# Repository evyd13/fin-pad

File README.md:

# Fin Pad

Replacement PCB for Lin Dolphin Pad.

## License

Read the license before use!

## Gerbers

Gerber zip files can be found under `gerber/`.

## BOM

| LCSC part # | Description   | Value | Package  | Amount |
| ----------- | ------------- | ----- | -------- | ------:|
| C14663      | Capacitor     | 0.1uF | 0603     | 3      |
| C19666      | Capacitor     | 4.7uF | 0603     | 1      |
| C15849      | Capacitor     | 1uF   | 0603     | 1      |
| C2128       | Switch diode  | 4148  | 0805     | 24     |
| C261942     | Fuse          |       | 0805     | 1      |
| C165948     | Type-C con.   |       | SMD+TH   | 1      |
| C25804      | Resistor      | 10K   | 0603     | 2      |
| C23345      | Resistor      | 22    | 0603     | 2      |
| C23186      | Resistor      | 5.1k  | 0603     | 2      |
| C7519       | ESD prot.     |       | SOT23-6  | 1      |
| C1337609    | MCU           | 32U2  | QFP-32   | 1      |
| C341521     | Resonator     | 16MHz | SMD      | 1      |
| C92584      | Switch        |       | SMD      | 1      |

Use at your own risk.

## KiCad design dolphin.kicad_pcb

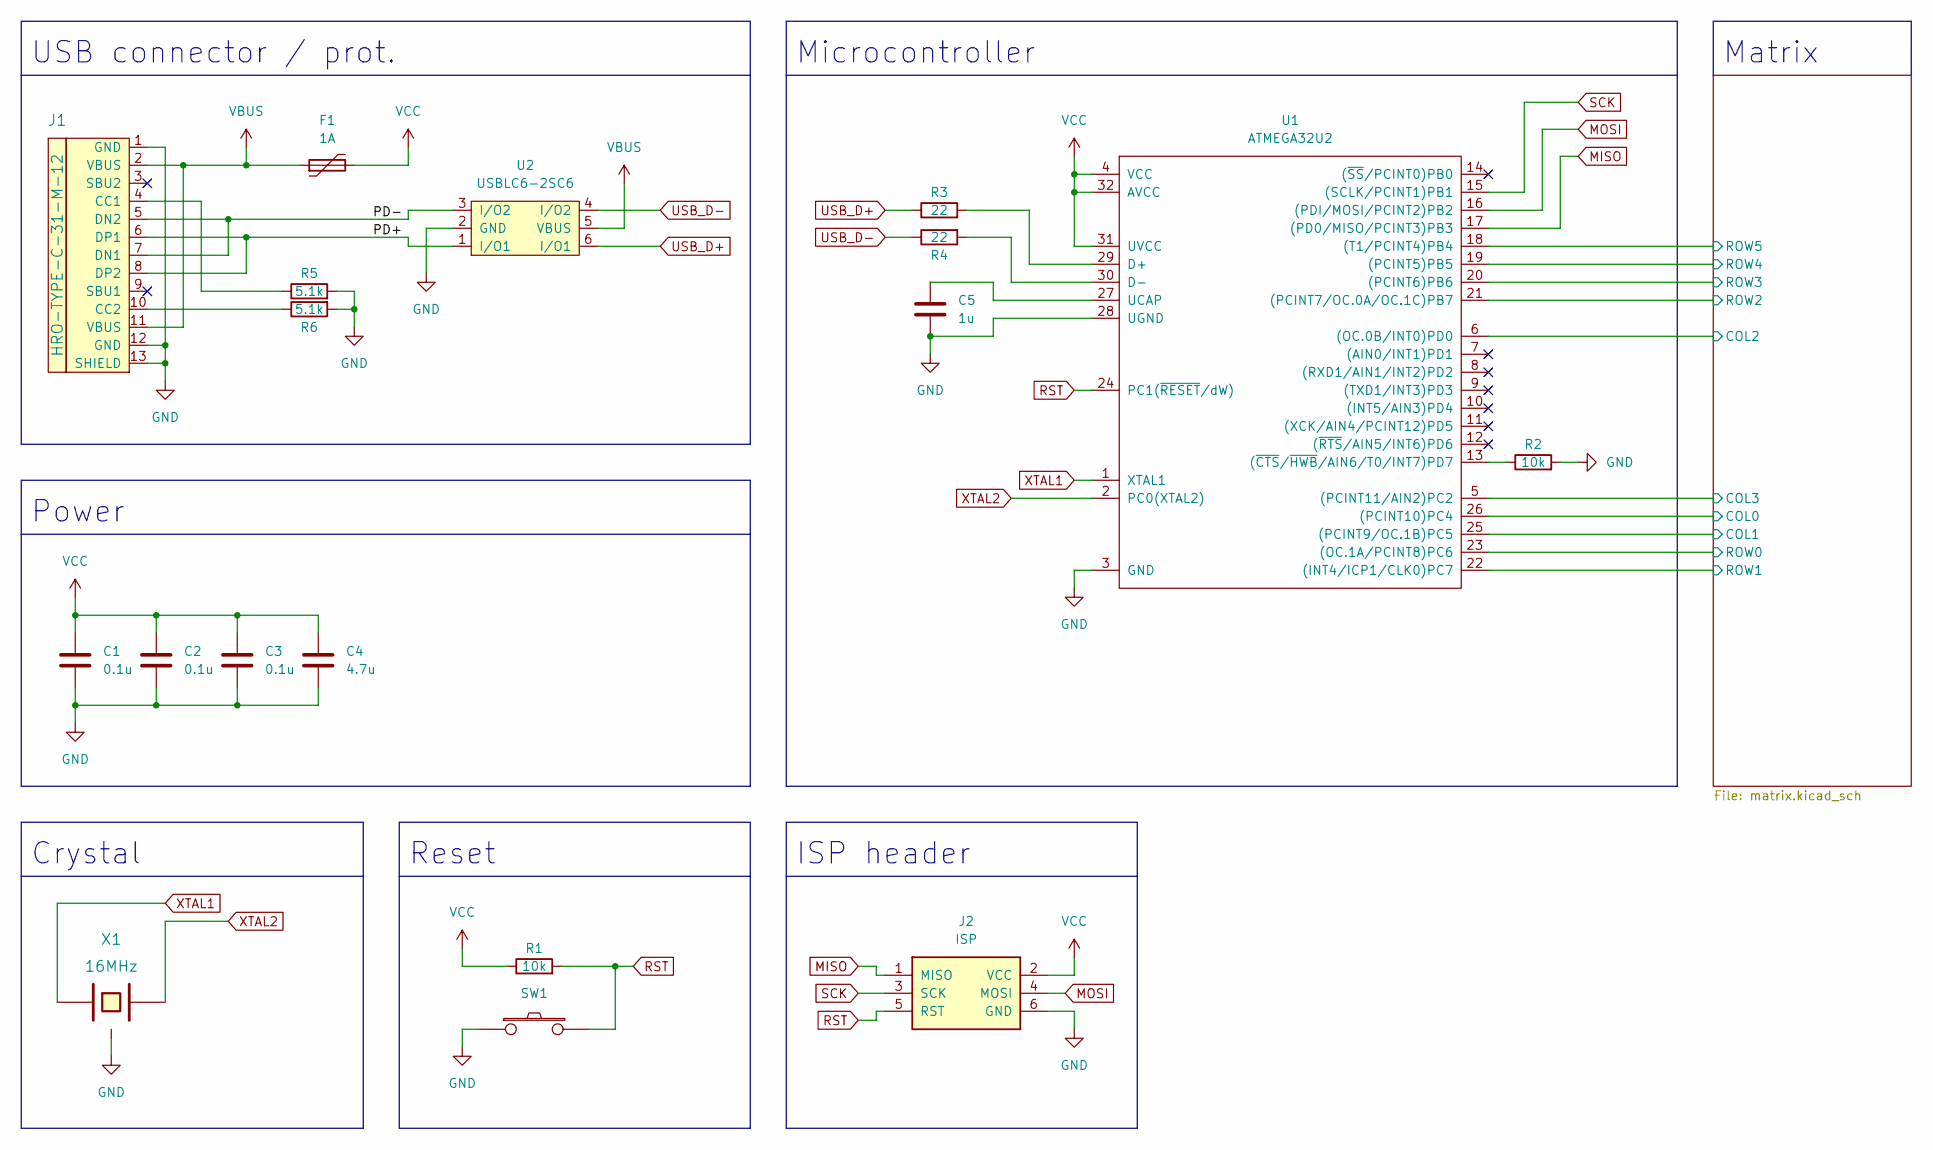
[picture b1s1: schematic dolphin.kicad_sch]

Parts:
C1, C2, C3: 0.1u; C_0603; Part number CC0603KRX7R9BB104; LCSC Part C14663
C4: 4.7u; C_0603; Part number CL10A475KO8NNNC; LCSC Part C19666
C5: 1u; C_0603; Part number CL10A105KB8NNNC; LCSC Part C15849
F1: 1A; R_0805; Part number TLC-PSMD050; LCSC Part C261942
J1: HRO-TYPE-C-31-M-12; CONN_HRO-TYPE-C-31-M-12; Part number TYPE-C-31-M-12; LCSC Part C165948
J2: ISP; CONN_isp_standard; JLCPCB BOM 0
R1, R2: 10k; R_0603; Part number 0603WAF1002T5E; LCSC Part C25804
R3, R4: 22; R_0603; Part number 0603WAF220JT5E; LCSC Part C23345
R5, R6: 5.1k; R_0603; Part number 0603WAF5101T5E; LCSC Part C23186
SW1: SW_PUSH; SWITCH_SPST_TL3342; Part number TS-1187A-B-A-B; LCSC Part C318884
U1: ATMEGA32U2; MCU_ATMEGA32U2-AU
U2: USBLC6-2SC6; PACKAGE_SOT-23-6; Part number USBLC6-2SC6; LCSC Part C7519
X1: 16MHz; XTAL_SMD_Murata_CSTxExxV-3Pin_3.0x1.1mm; Part number CSTNE16M0V530000R0; LCSC Part C341521

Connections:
/Matrix/COL0: U1.26 ((PCINT10)PC4); also elsewhere on the board
/Matrix/COL1: U1.25 ((PCINT9/OC.1B)PC5); also elsewhere on the board
/Matrix/COL2: U1.6 ((OC.0B/INT0)PD0); also elsewhere on the board
/Matrix/COL3: U1.5 ((PCINT11/AIN2)PC2); also elsewhere on the board
/Matrix/ROW0: U1.23 ((OC.1A/PCINT8)PC6); also elsewhere on the board
/Matrix/ROW1: U1.22 ((INT4/ICP1/CLK0)PC7); also elsewhere on the board
/Matrix/ROW2: U1.21 ((PCINT7/OC.0A/OC.1C)PB7); also elsewhere on the board
/Matrix/ROW3: U1.20 ((PCINT6)PB6); also elsewhere on the board
/Matrix/ROW4: U1.19 ((PCINT5)PB5); also elsewhere on the board
/Matrix/ROW5: U1.18 ((T1/PCINT4)PB4); also elsewhere on the board
/PD+: J1.6 (DP1), J1.8 (DP2), U2.1 (I/O1)
/PD-: J1.5 (DN2), J1.7 (DN1), U2.3 (I/O2)
GND: C1.2, C2.2, C3.2, C4.2, C5.2, J1.1 (GND), J1.12 (GND), J1.13 (SHIELD), J2.6 (GND), R2.2, R5.2, R6.2, SW1.1, U1.3 (GND), U1.28 (UGND), U2.2 (GND), X1.3
MISO: J2.1 (MISO), U1.17 ((PD0/MISO/PCINT3)PB3)
MOSI: J2.4 (MOSI), U1.16 ((PDI/MOSI/PCINT2)PB2)
unnamed: C5.1, U1.27 (UCAP)
unnamed: J1.4 (CC1), R5.1
unnamed: J1.10 (CC2), R6.1
unnamed: R2.1, U1.13 ((~CTS/~HWB/AIN6/T0/INT7)PD7)
unnamed: R3.2, U1.29 (D+)
unnamed: R4.2, U1.30 (D-)
RST: J2.5 (RST), R1.2, SW1.2, U1.24 (PC1(~RESET/dW))
SCK: J2.3 (SCK), U1.15 ((SCLK/PCINT1)PB1)
USB_D+: R3.1, U2.6 (I/O1)
USB_D-: R4.1, U2.4 (I/O2)
VBUS: F1.1, J1.2 (VBUS), J1.11 (VBUS), U2.5 (VBUS)
VCC: C1.1, C2.1, C3.1, C4.1, F1.2, J2.2 (VCC), R1.1, U1.4 (VCC), U1.31 (UVCC), U1.32 (AVCC)
XTAL1: U1.1 (XTAL1), X1.1
XTAL2: U1.2 (PC0(XTAL2)), X1.2

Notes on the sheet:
Matrix
Microcontroller
Power
Reset
ISP header
Crystal
USB connector / prot.

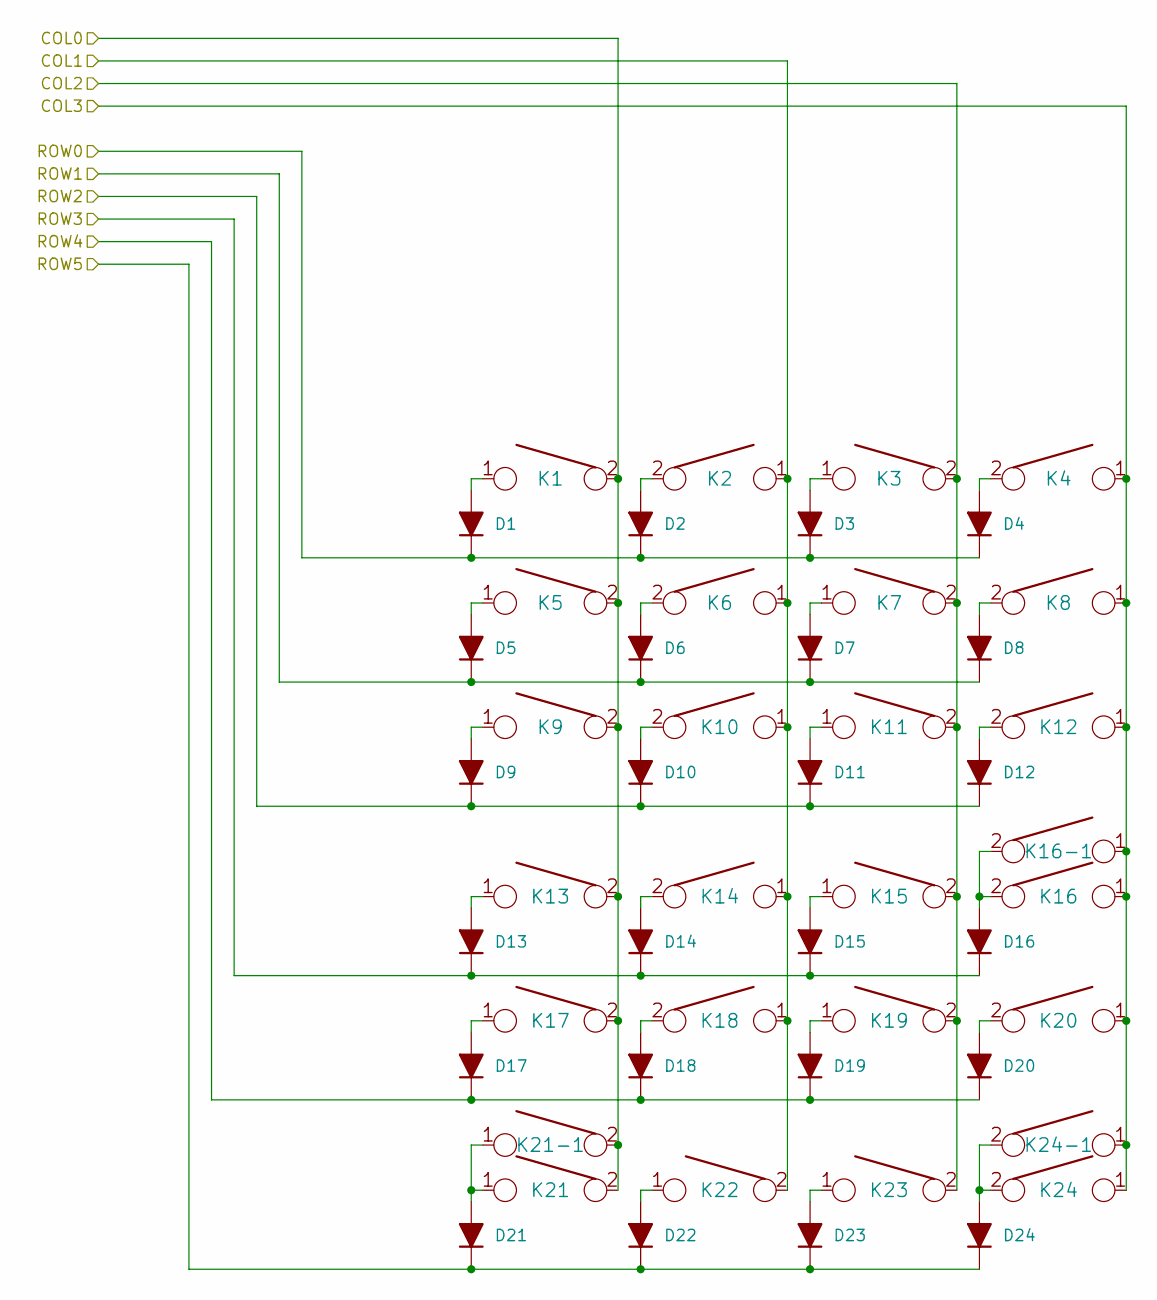
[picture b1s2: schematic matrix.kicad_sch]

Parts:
D1, D2, D3, D4, D5, D6, D7, D8, D9, D10, D11, D12, D13, D14, D15, D16, D17, D18, D19, D20, D21, D22, D23, D24: 4148; D_0805; Part number 1N4148WS; LCSC Part C2128
K1, K2, K3, K4, K5, K6, K7, K8, K9, K10, K11, K12, K13, K14, K15, K16, K17, K18, K19, K20, K21, K22, K23, K24: KEYSW; CHERRY_PLATE_100H; JLCPCB BOM 0
K16-1, K24-1: KEYSW; CHERRY_PCB_200H_V; JLCPCB BOM 0
K21-1: KEYSW; CHERRY_PCB_200H_F; JLCPCB BOM 0

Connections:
/Matrix/COL0: K1.2, K5.2, K9.2, K13.2, K17.2, K21.2, K21-1.2; also elsewhere on the board
/Matrix/COL1: K2.1, K6.1, K10.1, K14.1, K18.1, K22.2; also elsewhere on the board
/Matrix/COL2: K3.2, K7.2, K11.2, K15.2, K19.2, K23.2; also elsewhere on the board
/Matrix/COL3: K4.1, K8.1, K12.1, K16.1, K16-1.1, K20.1, K24.1, K24-1.1; also elsewhere on the board
/Matrix/ROW0: D1.1 (K), D2.1 (K), D3.1 (K), D4.1 (K); also elsewhere on the board
/Matrix/ROW1: D5.1 (K), D6.1 (K), D7.1 (K), D8.1 (K); also elsewhere on the board
/Matrix/ROW2: D9.1 (K), D10.1 (K), D11.1 (K), D12.1 (K); also elsewhere on the board
/Matrix/ROW3: D13.1 (K), D14.1 (K), D15.1 (K), D16.1 (K); also elsewhere on the board
/Matrix/ROW4: D17.1 (K), D18.1 (K), D19.1 (K), D20.1 (K); also elsewhere on the board
/Matrix/ROW5: D21.1 (K), D22.1 (K), D23.1 (K), D24.1 (K); also elsewhere on the board
unnamed: D1.2 (A), K1.1
unnamed: D2.2 (A), K2.2
unnamed: D3.2 (A), K3.1
unnamed: D4.2 (A), K4.2
unnamed: D5.2 (A), K5.1
unnamed: D6.2 (A), K6.2
unnamed: D7.2 (A), K7.1
unnamed: D8.2 (A), K8.2
unnamed: D9.2 (A), K9.1
unnamed: D10.2 (A), K10.2
unnamed: D11.2 (A), K11.1
unnamed: D12.2 (A), K12.2
unnamed: D13.2 (A), K13.1
unnamed: D14.2 (A), K14.2
unnamed: D15.2 (A), K15.1
unnamed: D16.2 (A), K16.2, K16-1.2
unnamed: D17.2 (A), K17.1
unnamed: D18.2 (A), K18.2
unnamed: D19.2 (A), K19.1
unnamed: D20.2 (A), K20.2
unnamed: D21.2 (A), K21.1, K21-1.1
unnamed: D22.2 (A), K22.1
unnamed: D23.2 (A), K23.1
unnamed: D24.2 (A), K24.2, K24-1.2

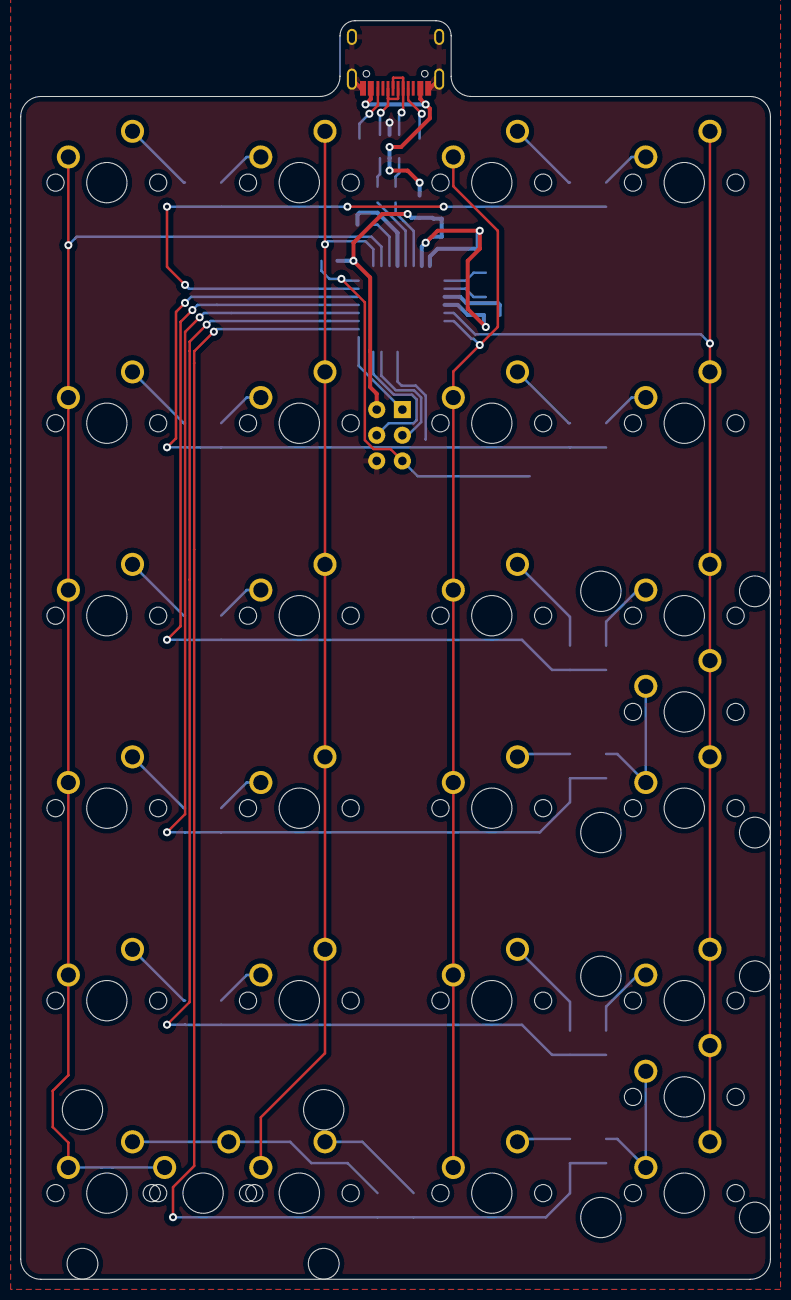
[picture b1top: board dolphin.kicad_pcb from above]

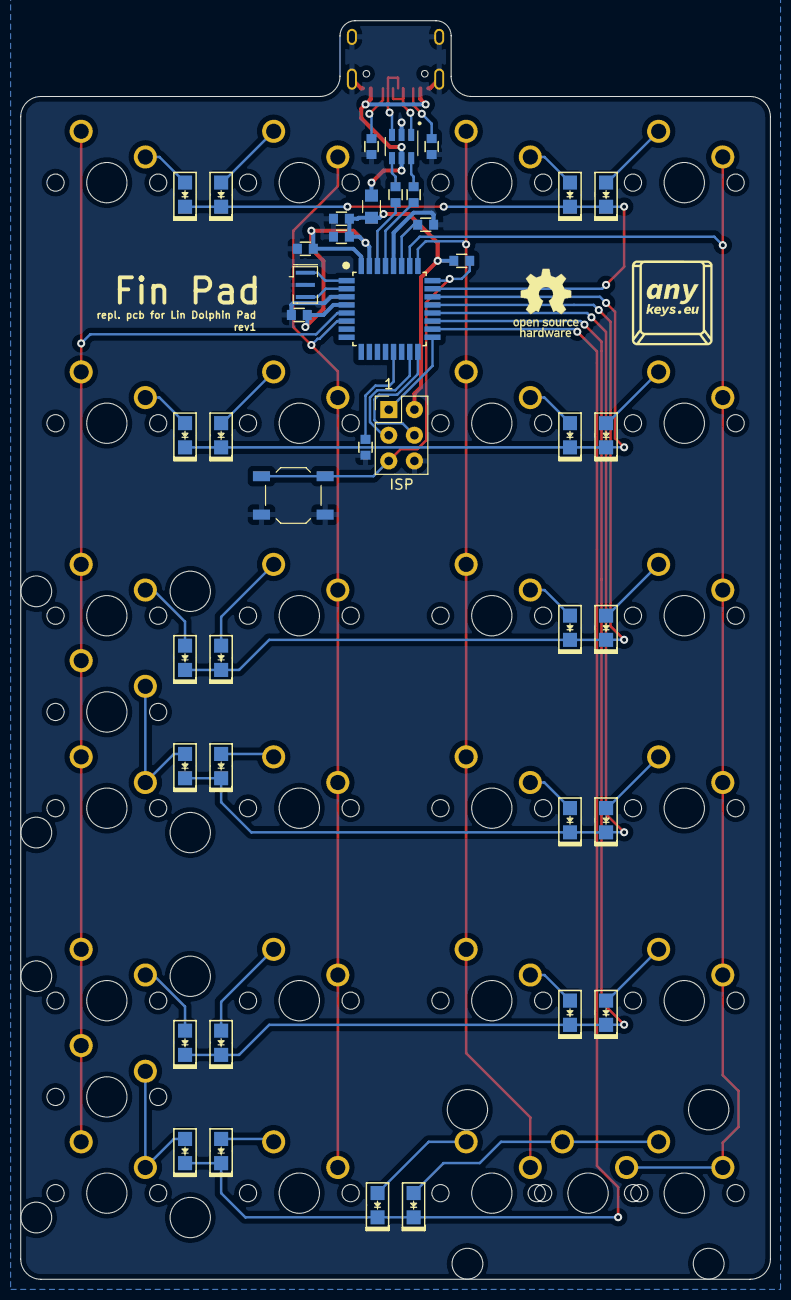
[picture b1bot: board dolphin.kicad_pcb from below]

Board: 2 copper layers, 74.2 x 124.6 mm, 69 parts (41 on the bottom side), 53 nets.

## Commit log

2022-07-01 Upload rev1 files
2022-07-01 Add BOM/readme
2022-07-01 Add gerber
